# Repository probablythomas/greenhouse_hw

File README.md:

# greenhouse_hw
KiCad design for automated greenhouse

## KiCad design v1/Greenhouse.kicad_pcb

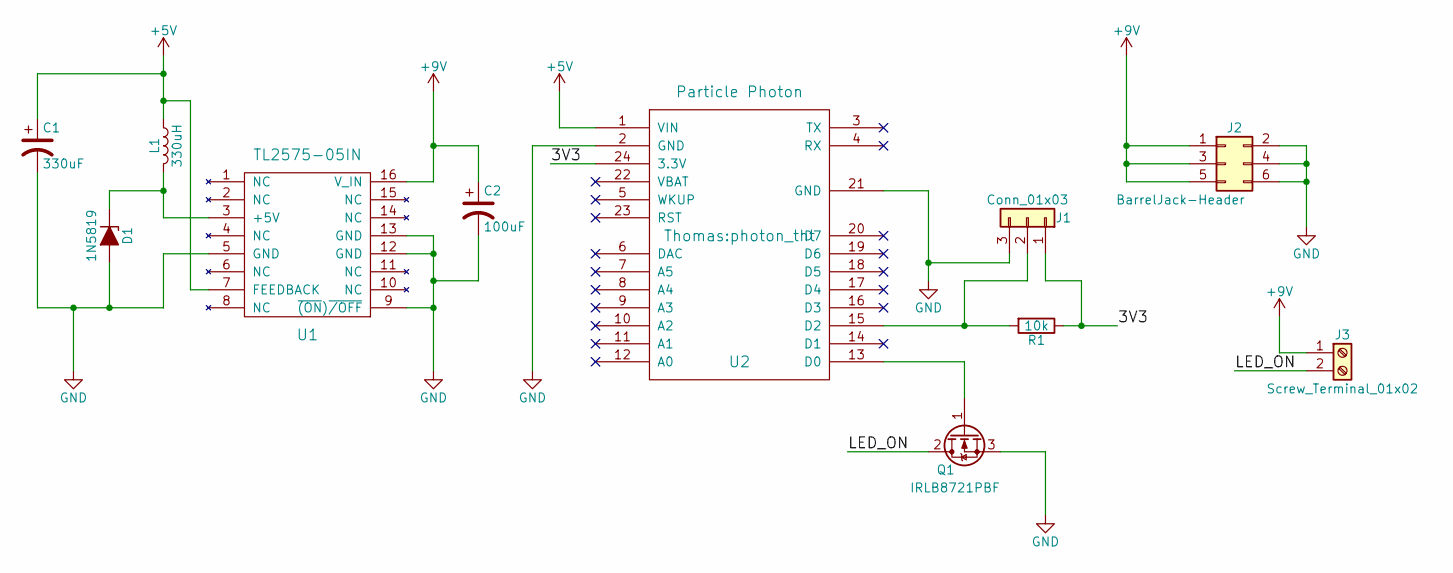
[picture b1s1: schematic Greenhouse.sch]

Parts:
C1: 330uF; CP_Radial_D6.3mm_P2.50mm
C2: 100uF; CP_Radial_D6.3mm_P2.50mm
D1: 1N5819; D_DO-41_SOD81_P10.16mm_Horizontal
J1: Conn_01x03; Pin_Header_Angled_1x03_Pitch2.54mm
J2: BarrelJack-Header; Barrel_Jack_Pin_Header_Straight_2x03_Pitch2.54mm
J3: Screw_Terminal_01x02; TerminalBlock_Phoenix_PT-3.5mm_2pol
L1: 330uH; L_Radial_D8.7mm_P5.00mm_Fastron_07HCP
Q1: IRLB8721PBF; TO-220-3_Horizontal_NO_HOLE
R1: 10k; R_Axial_DIN0207_L6.3mm_D2.5mm_P7.62mm_Horizontal
U1: TL2575-05IN; DIP-16_W7.62mm
U2: Particle Photon; photon_tht

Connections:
+5V: C1.1, L1.1, U1.7 (FEEDBACK), U2.1 (VIN)
+9V: C2.1, J2.1, J2.3, J2.5, J3.1, U1.16 (V_IN)
/3V3: J1.1, R1.1, U2.24 (3.3V)
/LED_ON: J3.2, Q1.2 (D)
GND: C1.2, C2.2, D1.2 (A), J1.3, J2.2, J2.4, J2.6, Q1.3 (S), U1.5 (GND), U1.9 (~(ON)~/OFF), U1.12 (GND), U1.13 (GND), U2.2 (GND), U2.21 (GND)
unnamed: D1.1 (K), L1.2, U1.3 (+5V)
unnamed: J1.2, R1.2, U2.15 (D2)
unnamed: Q1.1 (G), U2.13 (D0)

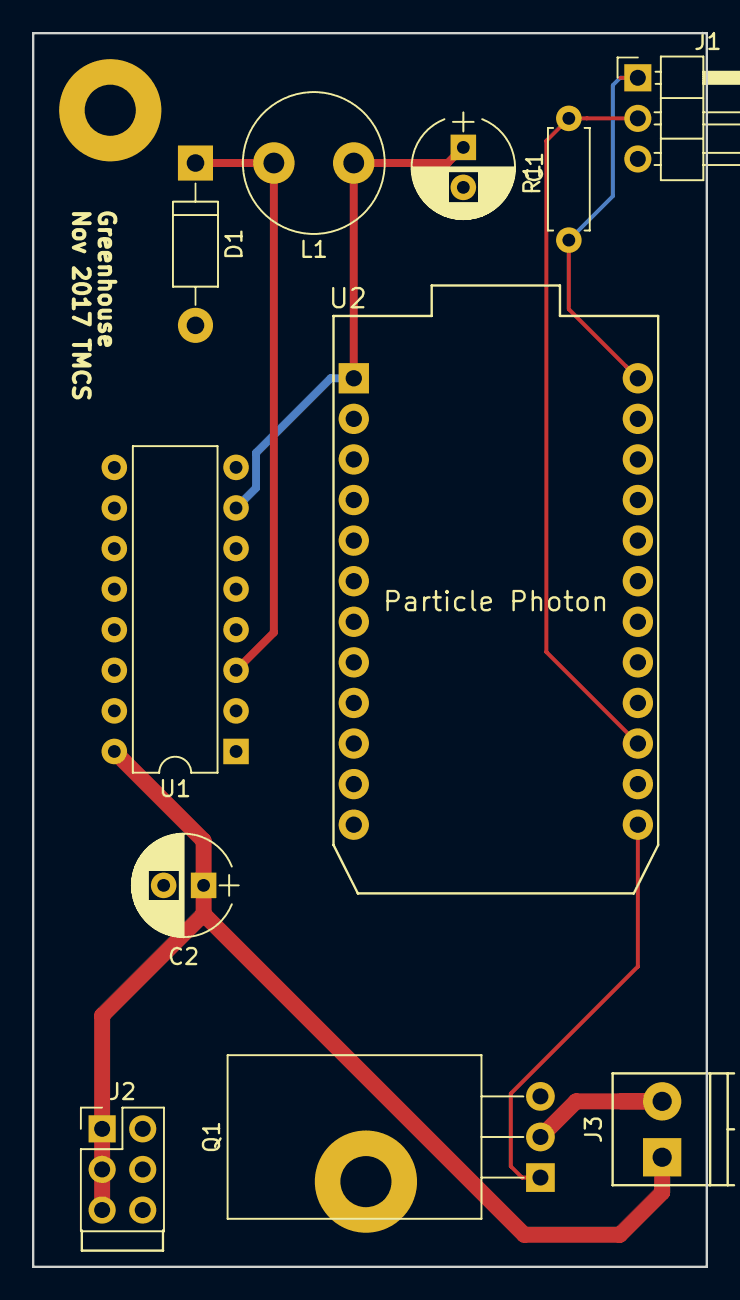
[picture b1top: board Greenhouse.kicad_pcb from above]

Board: 2 copper layers, 42.2 x 77.2 mm, 11 parts (0 on the bottom side), 8 nets.

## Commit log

2017-11-18 First commit for PCB files
2017-11-18 Renamed v1 to Hardware_v1 for clarity
